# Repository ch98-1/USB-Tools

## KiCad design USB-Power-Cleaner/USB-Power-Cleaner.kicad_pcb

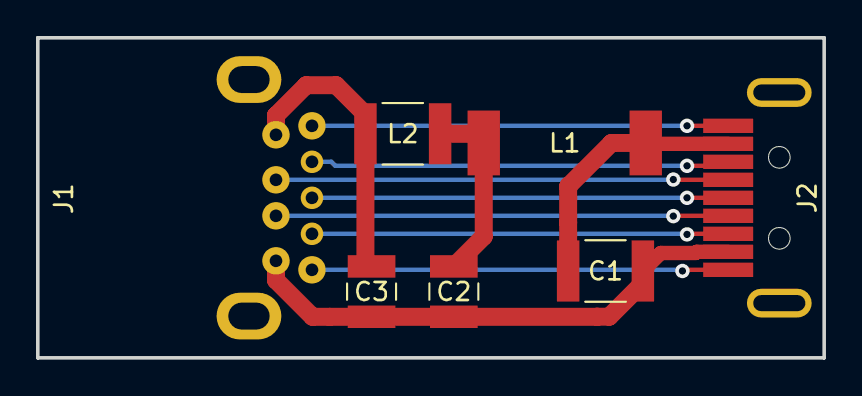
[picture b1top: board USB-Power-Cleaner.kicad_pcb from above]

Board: 2 copper layers, 43.7 x 17.8 mm, 7 parts (0 on the bottom side), 12 nets.

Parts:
C1: 0.1uF; C_1812_4532Metric
C2, C3: 100uF; C_1210_3225Metric
J1: USB3_A; USB_3_A_Recepticle_Amphenol_10117835-002LF
J2: USB3_A; USB_3_A_Plug_Amphenol_GSB316441CEU
L1: 100uH; SRU1048
L2: Ferrite_Bead; L_1812_4532Metric

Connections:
GND: C1.2, C2.2, C3.2, J1.4, J2.4
unnamed: C1.1, J2.1, L1.1
unnamed: C2.1, L1.2, L2.2
unnamed: C3.1, J1.1, L2.1
unnamed: J1.2, J2.2
unnamed: J1.3, J2.3
unnamed: J1.5, J2.5
unnamed: J1.6, J2.6
unnamed: J1.7, J2.7
unnamed: J1.8, J2.8
unnamed: J1.9, J2.9
unnamed: J1.10, J2.10

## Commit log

2018-06-11 Created slotted and slot free version of the USB voltage probe
2018-06-11 Created USB Power Cleaner that filters out switching noize
2018-06-11 Added BOM
2018-06-26 Changed stuff to work better on oshpark board constraints
